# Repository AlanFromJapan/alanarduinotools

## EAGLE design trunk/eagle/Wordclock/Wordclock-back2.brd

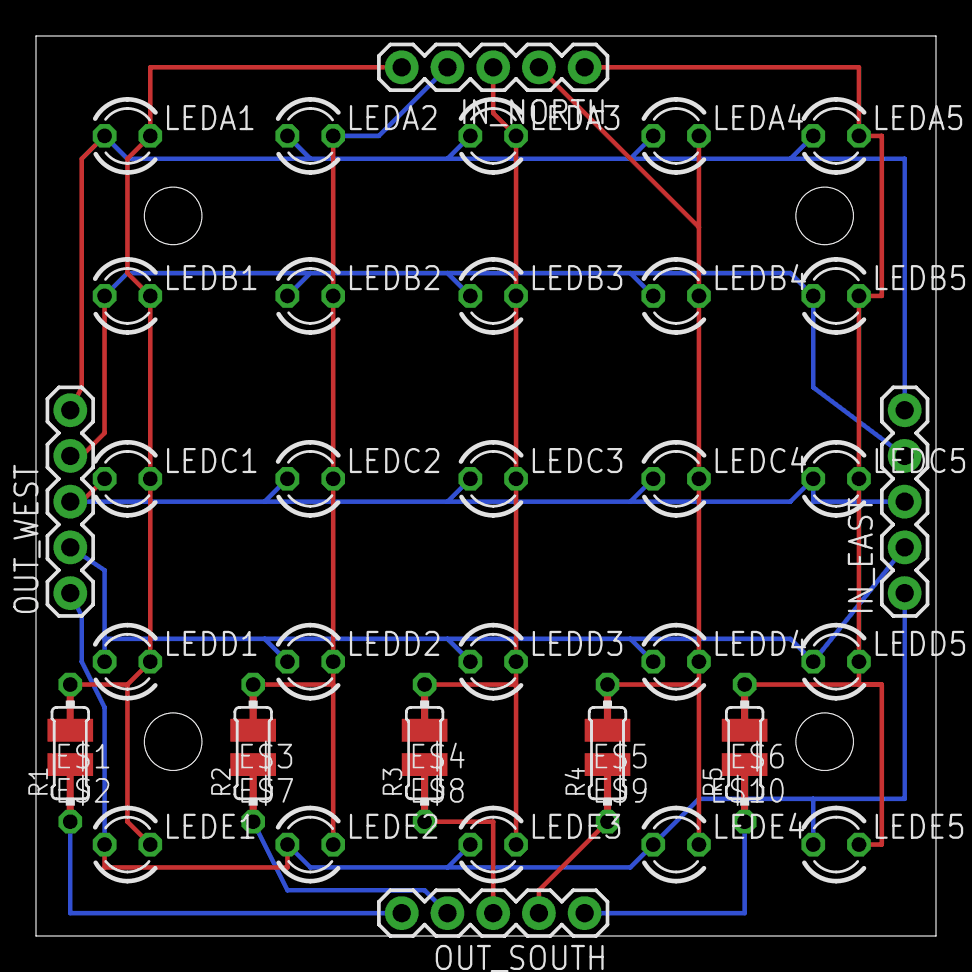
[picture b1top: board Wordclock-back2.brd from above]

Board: 2 copper layers, 50.0 x 50.0 mm, 44 parts (0 on the bottom side), 15 nets.

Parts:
E$1, E$2, E$3, E$4, E$5, E$6, E$7, E$8, E$9, E$10: SMD1,27-2,54
IN_EAST: 1X05
IN_NORTH: 1X05
LEDA1, LEDA2, LEDA3, LEDA4, LEDA5: LED3MM
LEDB1, LEDB2, LEDB3, LEDB4, LEDB5: LED3MM
LEDC1, LEDC2, LEDC3, LEDC4, LEDC5: LED3MM
LEDD1, LEDD2, LEDD3, LEDD4, LEDD5: LED3MM
LEDE1, LEDE2, LEDE3, LEDE4, LEDE5: LED3MM
OUT_SOUTH: 1X05
OUT_WEST: 1X05
R1, R2, R3, R4, R5: 0204/7

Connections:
unnamed: E$1.1, IN_NORTH.5, LEDA1.K, LEDB1.K, LEDC1.K, LEDD1.K, LEDE1.K, R1.2
unnamed: E$3.1, IN_NORTH.4, LEDA2.K, LEDB2.K, LEDC2.K, LEDD2.K, LEDE2.K, R2.2
unnamed: E$4.1, IN_NORTH.3, LEDA3.K, LEDB3.K, LEDC3.K, LEDD3.K, LEDE3.K, R3.2
unnamed: E$5.1, IN_NORTH.2, LEDA4.K, LEDB4.K, LEDC4.K, LEDD4.K, LEDE4.K, R4.2
unnamed: E$6.1, IN_NORTH.1, LEDA5.K, LEDB5.K, LEDC5.K, LEDD5.K, LEDE5.K, R5.2
unnamed: E$10.1, OUT_SOUTH.1, R5.1
unnamed: E$9.1, OUT_SOUTH.2, R4.1
unnamed: E$8.1, OUT_SOUTH.3, R3.1
unnamed: E$7.1, OUT_SOUTH.4, R2.1
unnamed: E$2.1, OUT_SOUTH.5, R1.1
unnamed: IN_EAST.5, LEDA1.A, LEDA2.A, LEDA3.A, LEDA4.A, LEDA5.A, OUT_WEST.5
unnamed: IN_EAST.4, LEDB1.A, LEDB2.A, LEDB3.A, LEDB4.A, LEDB5.A, OUT_WEST.4
unnamed: IN_EAST.3, LEDC1.A, LEDC2.A, LEDC3.A, LEDC4.A, LEDC5.A, OUT_WEST.3
unnamed: IN_EAST.2, LEDD1.A, LEDD2.A, LEDD3.A, LEDD4.A, LEDD5.A, OUT_WEST.2
unnamed: IN_EAST.1, LEDE1.A, LEDE2.A, LEDE3.A, LEDE4.A, LEDE5.A, OUT_WEST.1

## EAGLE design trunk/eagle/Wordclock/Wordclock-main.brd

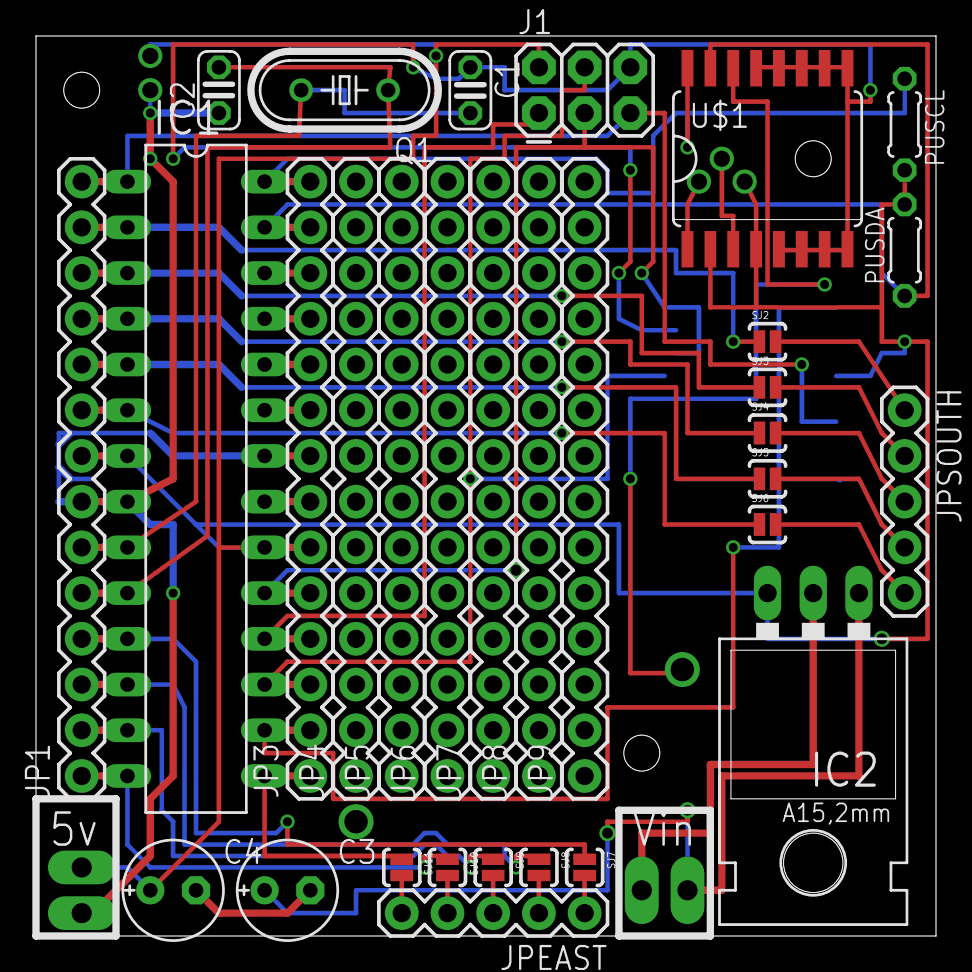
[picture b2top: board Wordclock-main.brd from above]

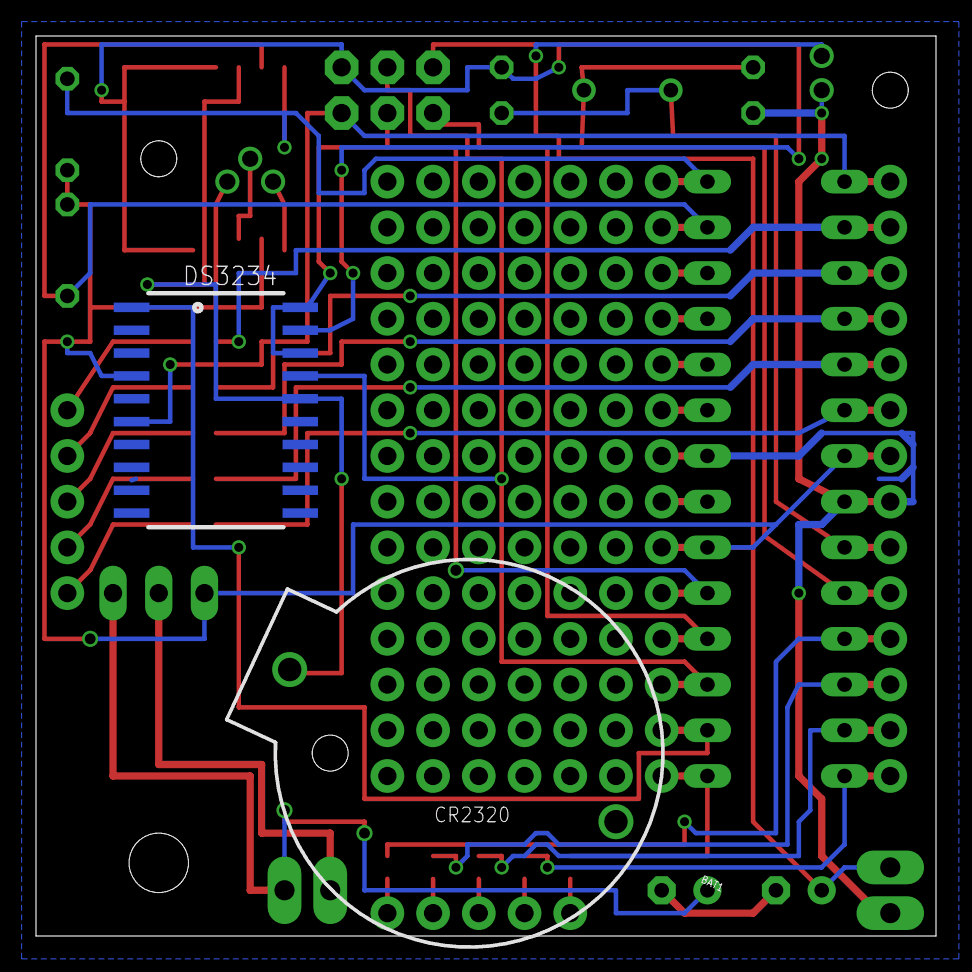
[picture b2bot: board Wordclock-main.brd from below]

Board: 2 copper layers, 50.0 x 50.0 mm, 35 parts (2 on the bottom side), 43 nets.

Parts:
5V: 1X02_LONGPADS
BAT1: BATTCOM_20MM_PTH
C1, C2: 22pF; C025-024X044
C3: 47u; E2,5-6E
C4: 4.7u; E2,5-6E
DS3234: DS3234
IC1: MEGA8-P; DIL28-3
IC2: 78XXL
J1: AVR_SPI_PRG_6PTH; 2X3
JP1, JP3, JP4, JP5, JP6, JP7, JP8, JP9: M14; 1X14
JPEAST: 1X05
JPSOUTH: 1X05
PUSCL: 10k; 0204/5
PUSDA: 10k; 0204/5
Q1: 16MHz; HC49/S
SJ2, SJ3, SJ4, SJ5, SJ6, SJ7, SJ8, SJ9, SJ10, SJ11: SOLDERJUMPERNO; SJ_2S-NO
U$1: DS3231; SO16W
UNREGULATED: 1X02_LONGPADS

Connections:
BATP: BAT1.1, DS3234.16, U$1.14
GND: 5V.1, BAT1.2, C1.1, C2.1, C3.-, C4.-, DS3234.2, DS3234.7, DS3234.8, DS3234.9, DS3234.10, DS3234.11, DS3234.12, DS3234.13, DS3234.14, DS3234.15, DS3234.19, IC1.8, IC1.22, IC2.GND, J1.6, JP1.7, JP3.8, UNREGULATED.1
unnamed: JPEAST.1, SJ7.2
unnamed: C1.2, IC1.9, JP1.6, Q1.2
unnamed: C2.2, IC1.10, JP1.5, Q1.1
unnamed: IC1.16, JP3.2
unnamed: JPEAST.2, SJ8.2
unnamed: JPEAST.3, SJ9.2
unnamed: JPEAST.4, SJ10.2
unnamed: JPEAST.5, SJ11.2
unnamed: DS3234.18, DS3234.20, IC1.19, J1.3, JP3.5
unnamed: DS3234.17, IC1.17, J1.4, JP3.3
unnamed: JPSOUTH.1, SJ2.2
unnamed: JPSOUTH.2, SJ3.2
unnamed: JPSOUTH.3, SJ4.2
unnamed: JPSOUTH.4, SJ5.2
unnamed: JPSOUTH.5, SJ6.2
unnamed: IC1.2, JP1.13, SJ2.1
unnamed: IC1.3, JP1.12, SJ3.1
unnamed: IC1.4, JP1.11, SJ4.1
unnamed: IC1.5, JP1.10, SJ5.1
unnamed: IC1.6, JP1.9, SJ6.1
unnamed: IC1.15, JP3.1, SJ11.1
unnamed: IC1.14, JP1.1, SJ10.1
unnamed: IC1.13, JP1.2, SJ9.1
unnamed: IC1.12, JP1.3, SJ8.1
unnamed: IC1.11, JP1.4, SJ7.1
unnamed: IC1.28, JP3.14, PUSCL.1
unnamed: IC1.27, JP3.13, PUSDA.1, U$1.15
RESET: DS3234.6, IC1.1, J1.5, JP1.14
S$1: IC1.18, J1.1, JP3.4
S$2: IC1.26, JP3.12
S$3: IC1.25, JP3.11
S$4: IC1.24, JP3.10
S$5: IC1.23, JP3.9
S$6: IC1.21, JP3.7
S$7: U$1.12, U$1.13
S$8: U$1.7, U$1.8
S$9: U$1.5, U$1.6
S$11: U$1.9, U$1.10, U$1.11
S$12: U$1.2, U$1.4
VCC: 5V.2, C4.+, DS3234.4, IC1.7, IC1.20, IC2.OUT, J1.2, JP1.8, JP3.6, PUSCL.2, PUSDA.2
VIN: C3.+, IC2.IN, UNREGULATED.2

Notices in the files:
parts and their libraries:
SparkFun: Licensing: CC v3.0 Share-Alike You are welcome to use this library for commercial purposes.
